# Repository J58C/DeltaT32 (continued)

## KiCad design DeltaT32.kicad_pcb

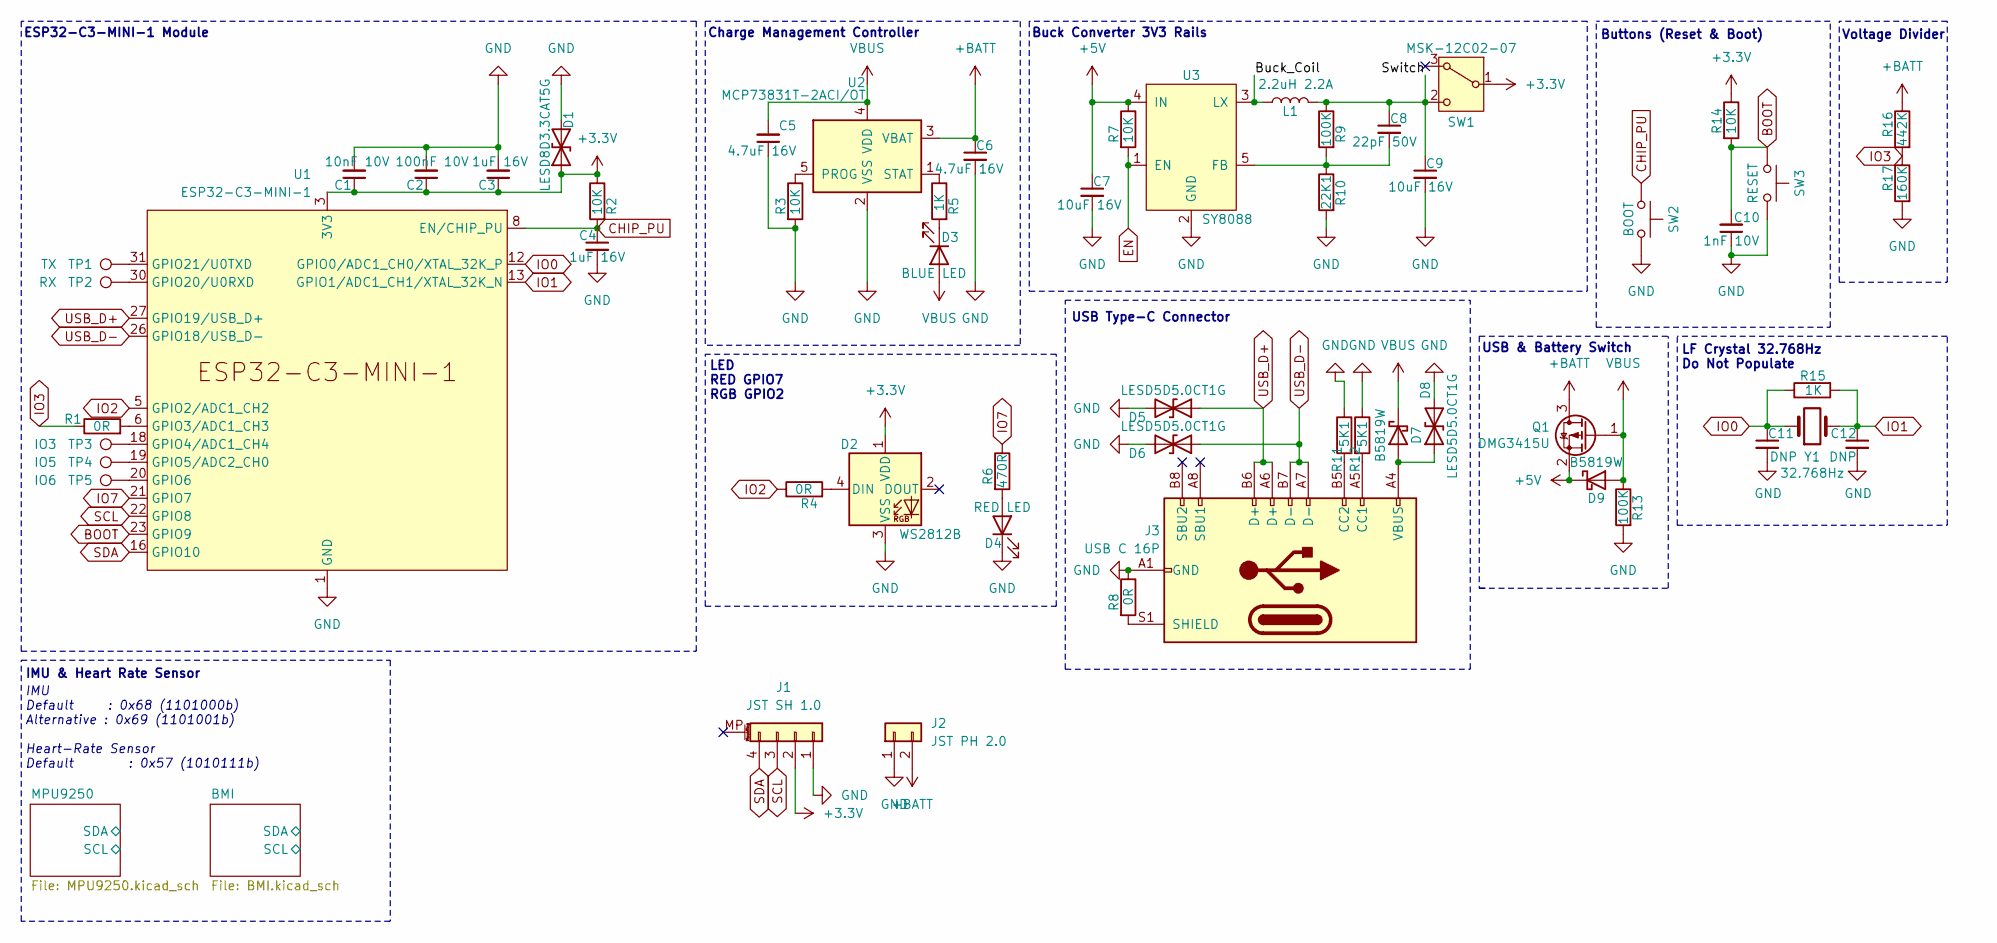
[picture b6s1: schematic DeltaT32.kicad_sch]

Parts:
C1: 10nF 10V; C_0402_1005Metric; LCSC C15195
C2: 100nF 10V; C_0402_1005Metric; LCSC C1525
C3, C4: 1uF 16V; C_0402_1005Metric; LCSC C52923
C5, C6: 4.7uF 16V; C_0603_1608Metric; LCSC C19666
C7, C9: 10uF 16V; C_0805_2012Metric; LCSC C15850
C8: 22pF 50V; C_0603_1608Metric; LCSC C1653
C10: 1nF 10V; C_0402_1005Metric; LCSC C1523
C11, C12: DNP; C_0402_1005Metric
D1: LESD8D3.3CAT5G; D_SOD-882; LCSC C172409
D2: WS2812B; LED_WS2812B-2020_PLCC4_2.0x2.0mm
D3: BLUE LED; LED_0603_1608Metric
D4: RED LED; LED_0603_1608Metric; LCSC C2286
D5, D6, D8: LESD5D5.0CT1G; D_SOD-523; LCSC C383211
D7, D9: B5819W; D_SOD-123; LCSC C8598
J1: JST SH 1.0; JST_SH_SM04B-SRSS-TB_1x04-1MP_P1.00mm_Horizontal
J2: JST PH 2.0; JST_PH_S2B-PH-K_1x02_P2.00mm_Horizontal
J3: USB C 16P; USB_C_Receptacle_GCT_USB4105-xx-A_16P_TopMnt_Horizontal
L1: 2.2uH 2.2A; L_Bourns-SRN4018; LCSC C370436
Q1: DMG3415U; SOT-23; LCSC C96616
R1, R4, R8: 0R; R_0402_1005Metric
R2, R3, R7, R14: 10K; R_0402_1005Metric
R5, R15: 1K; R_0402_1005Metric
R6: 470R; R_0402_1005Metric
R9, R13: 100K; R_0402_1005Metric
R10: 22K1; R_0402_1005Metric
R11, R12: 5K1; R_0402_1005Metric
R16: 442K; R_0805_2012Metric
R17: 160K; R_0805_2012Metric
SW1: MSK-12C02-07; SW_SPDT_PCM12
SW2: BOOT; SW_Push_SPST_NO_Alps_SKRK
SW3: RESET; SW_Push_SPST_NO_Alps_SKRK
TP1: TX; TestPoint_Pad_D1.0mm
TP2: RX; TestPoint_Pad_D1.0mm
TP3: IO3; TestPoint_Pad_D1.0mm
TP4: IO5; TestPoint_Pad_D1.0mm
TP5: IO6; TestPoint_Pad_D1.0mm
U1: ESP32-C3-MINI-1
U2: MCP73831T-2ACI/OT; SOT-23-5; LCSC C424093
U3: SY8088; SOT-23-5; LCSC C479072
Y1: 32.768Hz; Crystal_SMD_3215-2Pin_3.2x1.5mm

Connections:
+3.3V: C1.1, C2.1, C3.1, D1.1 (A1), D2.1 (VDD), J1.2, R2.1, R14.1, SW1.1 (B), U1.3 (3V3)
+5V: C7.1, D9.1 (K), Q1.2 (S), R7.1, U3.4 (IN)
+BATT: C6.1, J2.2, Q1.3 (D), R16.1, U2.3 (VBAT)
/Buck_Coil: L1.1, U3.3 (LX)
/Switch: C8.1, C9.1, L1.2, R9.1, SW1.2 (C)
BOOT: C10.2, R14.2, SW3.1, U1.23 (GPIO9)
CHIP_PU: C4.1, R2.2, SW2.1, U1.8 (EN/CHIP_PU)
EN: R7.2, U3.1 (EN)
GND: C1.2, C2.2, C3.2, C4.2, C5.1, C6.2, C7.2, C9.2, C10.1, C11.2, C12.2, D1.2 (A2), D2.3 (VSS), D4.1 (K), D5.2 (A2), D6.2 (A2), D8.2 (A2), J1.1, J2.1, J3.A1 (GND), J3.A12 (GND), J3.B1 (GND), J3.B12 (GND), R3.2, R8.1, R10.2, R11.1, R12.1, R13.2, R17.2, SW2.2, SW3.2, U1.1 (GND), U1.2 (GND), U1.11 (GND), U1.14 (GND), U1.36 (GND), U1.37 (GND), U1.38 (GND), U1.39 (GND), U1.40 (GND), U1.41 (GND), U1.42 (GND), U1.43 (GND), U1.44 (GND), U1.45 (GND), U1.46 (GND), U1.47 (GND), U1.48 (GND), U1.49 (GND), U1.50 (GND), U1.51 (GND), U1.52 (GND), U1.53 (GND), U2.2 (VSS), U3.2 (GND); also elsewhere on the board
IO0: C11.1, R15.1, U1.12 (GPIO0/ADC1_CH0/XTAL_32K_P), Y1.1
IO1: C12.1, R15.2, U1.13 (GPIO1/ADC1_CH1/XTAL_32K_N), Y1.2
IO2: R4.1, U1.5 (GPIO2/ADC1_CH2)
IO3: R1.1, R16.2, R17.1
IO7: R6.1, U1.21 (GPIO7)
unnamed: D2.4 (DIN), R4.2
unnamed: D3.1 (K), R5.2
unnamed: D4.2 (A), R6.2
unnamed: D7.2 (A), D8.1 (A1), J3.A4 (VBUS), J3.A9 (VBUS), J3.B4 (VBUS), J3.B9 (VBUS)
unnamed: J3.A5 (CC1), R12.2
unnamed: J3.B5 (CC2), R11.2
unnamed: J3.S1 (SHIELD), R8.2
unnamed: R1.2, U1.6 (GPIO3/ADC1_CH3)
unnamed: TP3.1, U1.18 (GPIO4/ADC1_CH4)
unnamed: TP4.1, U1.19 (GPIO5/ADC2_CH0)
unnamed: TP5.1, U1.20 (GPIO6)
unnamed: TP2.1, U1.30 (GPIO20/U0RXD)
unnamed: TP1.1, U1.31 (GPIO21/U0TXD)
unnamed: R3.1, U2.5 (PROG)
unnamed: R5.1, U2.1 (STAT)
unnamed: C8.2, R9.2, R10.1, U3.5 (FB)
SCL: J1.3, U1.22 (GPIO8); also elsewhere on the board
SDA: J1.4, U1.16 (GPIO10); also elsewhere on the board
USB_D+: D5.1 (A1), J3.A6 (D+), J3.B6 (D+), U1.27 (GPIO19/USB_D+)
USB_D-: D6.1 (A1), J3.A7 (D-), J3.B7 (D-), U1.26 (GPIO18/USB_D-)
VBUS: C5.2, D3.2 (A), D7.1 (K), D9.2 (A), Q1.1 (G), R13.1, U2.4 (VDD)

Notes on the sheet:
Buck Converter 3V3 Rails
Voltage Divider
IMU & Heart Rate Sensor
Buttons (Reset & Boot)
Charge Management Controller
USB & Battery Switch
LF Crystal 32.768Hz Do Not Populate
USB Type-C Connector
IMU Default : 0x68 (1101000b) Alternative : 0x69 (1101001b) Heart-Rate Sensor Default : 0x57 (1010111b)
ESP32-C3-MINI-1 Module
LED RED GPIO7 RGB GPIO2

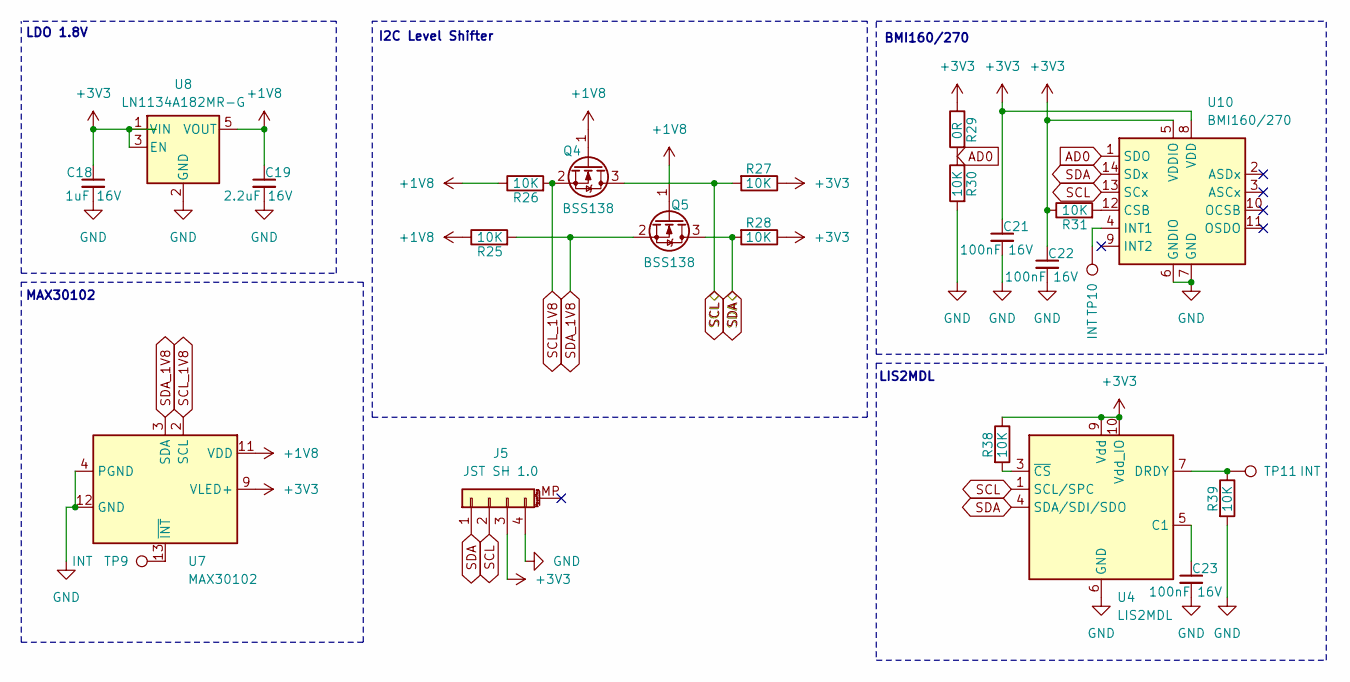
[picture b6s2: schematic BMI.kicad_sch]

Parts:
C18: 1uF 16V; C_0603_1608Metric
C19: 2.2uF 16V; C_0603_1608Metric
C21, C22, C23: 100nF 16V; C_0603_1608Metric
J5: JST SH 1.0; JST_SH_SM04B-SRSS-TB_1x04-1MP_P1.00mm_Horizontal
Q4, Q5: BSS138; SOT-23
R25, R26, R27, R28, R31, R38, R39: 10K; R_0603_1608Metric
R29: 0R; R_0402_1005Metric
R30: 10K; R_0402_1005Metric
TP9, TP10, TP11: INT; TestPoint_Pad_D1.0mm
U4: LIS2MDL; LGA-12_2x2mm_P0.5mm
U7: MAX30102; Maxim_OLGA-14_3.3x5.6mm_P0.8mm
U8: LN1134A182MR-G; SOT-23-5
U10: BMI160/270; Bosch_LGA-14_3x2.5mm_P0.5mm; LCSC C2836813

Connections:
+1V8: C19.1, Q4.1 (G), Q5.1 (G), R25.1, R26.1, U7.11 (VDD), U8.5 (VOUT); also elsewhere on the board
AD0: R29.2, R30.1, U10.1 (SDO); also elsewhere on the board
GND: C18.2, C19.2, C21.2, C22.2, C23.2, J5.4, R30.2, R39.2, U4.6 (GND), U4.8 (GND), U7.4 (PGND), U7.12 (GND), U8.2 (GND), U10.6 (GNDIO), U10.7 (GND); also elsewhere on the board
unnamed: C23.1, U4.5 (C1)
unnamed: R39.1, TP11.1, U4.7 (DRDY)
unnamed: R38.2, U4.3 (~CS)
unnamed: TP9.1, U7.13 (~INT)
unnamed: R31.2, U10.12 (CSB)
unnamed: TP10.1, U10.4 (INT1)
SCL: J5.2, Q4.3 (D), R27.2, U4.1 (SCL/SPC), U10.13 (SCx); also elsewhere on the board
SCL_1V8: Q4.2 (S), R26.2, U7.2 (SCL); also elsewhere on the board
SDA: J5.1, Q5.3 (D), R28.2, U4.4 (SDA/SDI/SDO), U10.14 (SDx); also elsewhere on the board
SDA_1V8: Q5.2 (S), R25.2, U7.3 (SDA); also elsewhere on the board
VDDIO: C18.1, C21.1, C22.1, J5.3, R27.1, R28.1, R29.1, R31.1, R38.1, U4.9 (Vdd), U4.10 (Vdd_IO), U7.9 (VLED+), U7.10 (VLED+), U8.1 (VIN), U8.3 (EN), U10.5 (VDDIO), U10.8 (VDD); also elsewhere on the board

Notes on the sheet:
MAX30102
LIS2MDL
LDO 1.8V
BMI160/270
I2C Level Shifter

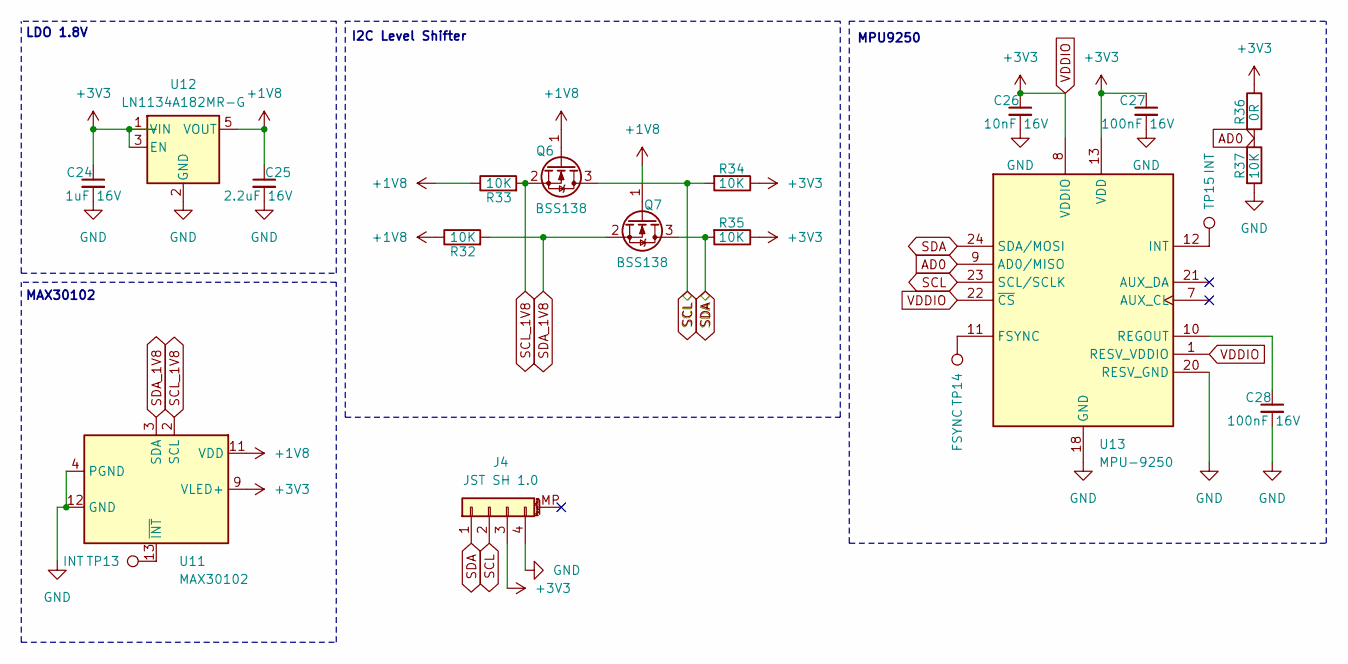
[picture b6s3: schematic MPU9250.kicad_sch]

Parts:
C24: 1uF 16V; C_0603_1608Metric
C25: 2.2uF 16V; C_0603_1608Metric
C26: 10nF 16V; C_0603_1608Metric
C27, C28: 100nF 16V; C_0603_1608Metric
J4: JST SH 1.0; JST_SH_SM04B-SRSS-TB_1x04-1MP_P1.00mm_Horizontal
Q6, Q7: BSS138; SOT-23
R32, R33, R34, R35: 10K; R_0603_1608Metric
R36: 0R; R_0402_1005Metric
R37: 10K; R_0402_1005Metric
TP13, TP15: INT; TestPoint_Pad_D1.0mm
TP14: FSYNC; TestPoint_Pad_D1.0mm
U11: MAX30102; Maxim_OLGA-14_3.3x5.6mm_P0.8mm
U12: LN1134A182MR-G; SOT-23-5
U13: MPU-9250; InvenSense_QFN-24_3x3mm_P0.4mm_NoMask

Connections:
+1V8: C25.1, Q6.1 (G), Q7.1 (G), R32.1, R33.1, U11.11 (VDD), U12.5 (VOUT); also elsewhere on the board
AD0: R36.2, R37.1, U13.9 (AD0/MISO); also elsewhere on the board
GND: C24.2, C25.2, C26.2, C27.2, C28.2, J4.4, R37.2, U11.4 (PGND), U11.12 (GND), U12.2 (GND), U13.18 (GND), U13.20 (RESV_GND); also elsewhere on the board
unnamed: TP13.1, U11.13 (~INT)
unnamed: TP14.1, U13.11 (FSYNC)
unnamed: TP15.1, U13.12 (INT)
unnamed: C28.1, U13.10 (REGOUT)
SCL: J4.2, Q6.3 (D), R34.2, U13.23 (SCL/SCLK); also elsewhere on the board
SCL_1V8: Q6.2 (S), R33.2, U11.2 (SCL); also elsewhere on the board
SDA: J4.1, Q7.3 (D), R35.2, U13.24 (SDA/MOSI); also elsewhere on the board
SDA_1V8: Q7.2 (S), R32.2, U11.3 (SDA); also elsewhere on the board
VDDIO: C24.1, C26.1, C27.1, J4.3, R34.1, R35.1, R36.1, U11.9 (VLED+), U11.10 (VLED+), U12.1 (VIN), U12.3 (EN), U13.1 (RESV_VDDIO), U13.8 (VDDIO), U13.13 (VDD), U13.22 (~CS); also elsewhere on the board

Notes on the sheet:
MAX30102
LDO 1.8V
MPU9250
I2C Level Shifter

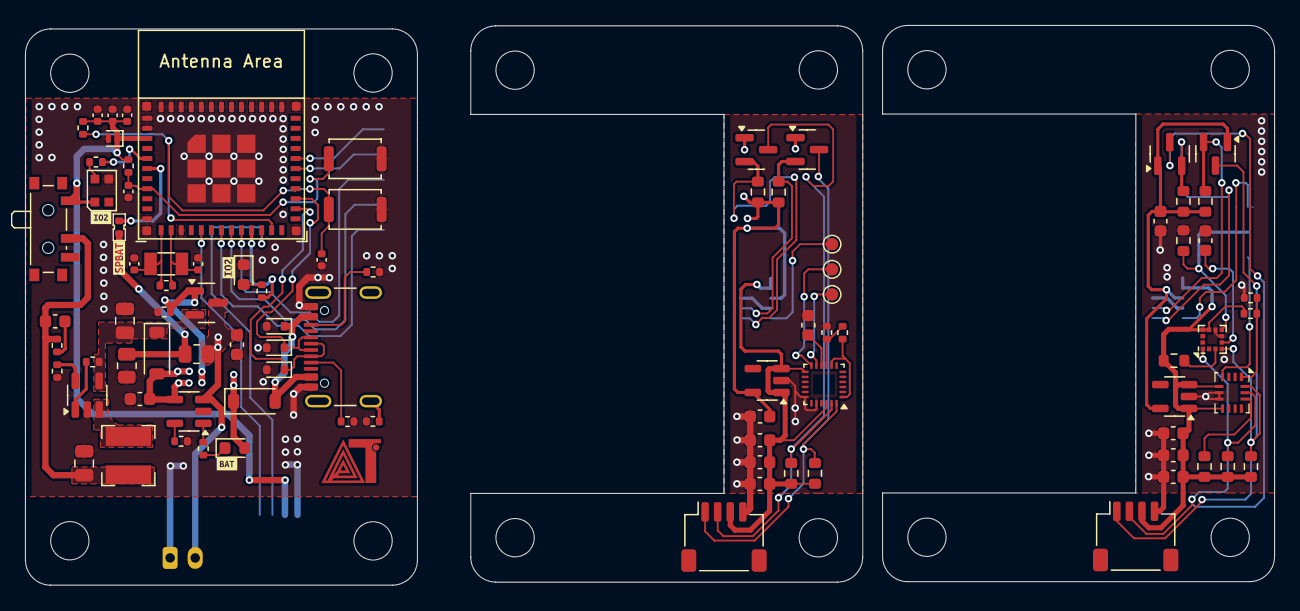
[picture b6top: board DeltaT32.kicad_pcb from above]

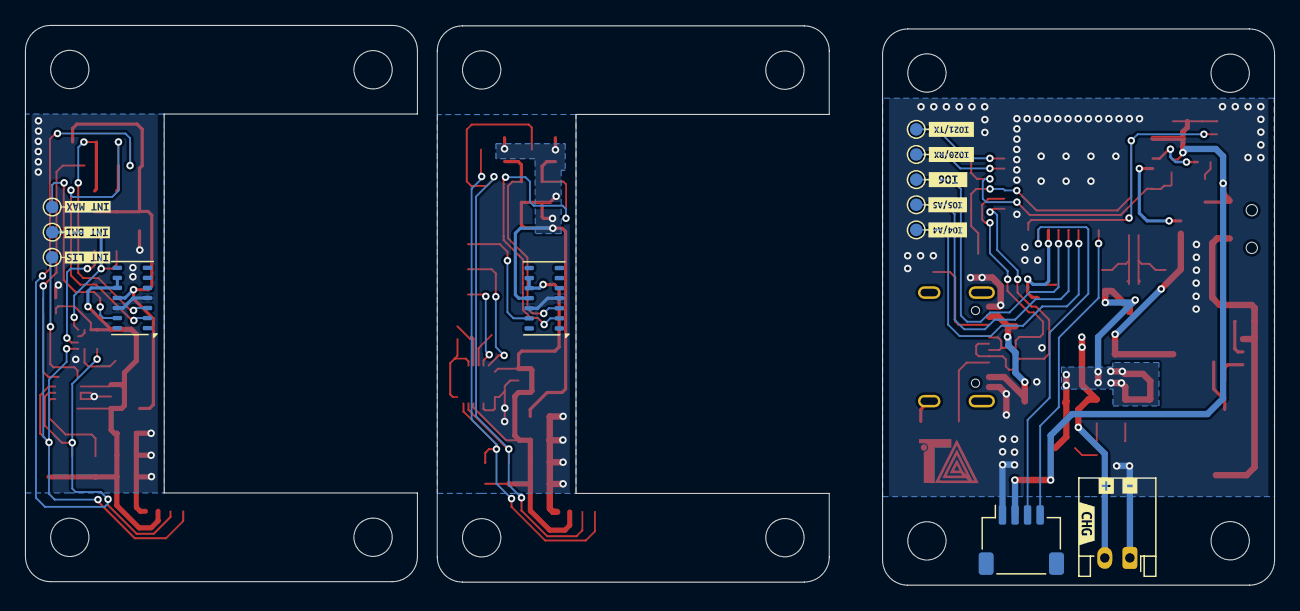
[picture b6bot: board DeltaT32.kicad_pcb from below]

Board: 2 copper layers, 99.4 x 44.5 mm, 103 parts (12 on the bottom side), 50 nets.

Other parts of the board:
kibuzzard-61C05335: G***; label
kibuzzard-67F4E109: G***; kibuzzard-67F4E109
kibuzzard-67FF2A33: G***; kibuzzard-67FF2A33
kibuzzard-6269032F: G***; kibuzzard-6269032F

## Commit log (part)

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2025-01-29 Twea
2025-01-29 Tweak
2025-01-29 Fix images workflow
2025-01-29 Update PCB render images for branch 17048
2025-01-29 Test
2025-01-29 Inital commit
2025-01-29 Initial file
2025-01-29 Update PCB render images
2025-01-29 Sync from 42 to main/42
2025-01-29 Sync from 17048 to main/17048
2025-01-29 Sync from 340 to main/340
2025-01-29 Create gif,yaml
2025-01-29 Update gif,yaml
2025-01-30 Add archive: 42-3001251053 from branch 42
2025-01-30 Add archive: Branch42-3001251058 from branch 42
2025-01-30 Add archive: Caps32Project-42-3001251131 from branch 42
2025-01-30 Update archive: Caps32Project-42-3001251133 from branch 42
2025-01-30 Update archive: Caps32Project-702-3001251140 from branch 702
2025-01-30 Update archive: Caps32Project-340-3001251202 from branch 340
2025-01-30 Update archive: Caps32Project-17048-3001251210 from branch 17048
2025-01-30 Update archive: Caps32Project-42-3001251211 from branch 42
2025-01-30 Update archive: Caps32Project-42-3001251311 from branch 42
2025-01-30 Update archive: Caps32Project-42-3001251318 from branch 42
2025-01-30 Update archive: Caps32Project-42-3001251326 from branch 42
2025-01-30 Update archive: Caps32Project-42-3001251333 from branch 42
2025-01-30 Update archive: Caps32Project-42-3001251345 from branch 42
2025-01-30 Update archive: Caps32Project-42-3001251407 from branch 42
2025-01-30 Move PCB render images from branch 42 to Images/42
2025-01-30 Update archive: Caps32Project-42-3001251414 from branch 42
2025-01-30 Update archive: Caps32Project-42-3001251421 from branch 42
2025-01-30 Update archive: Caps32Project-42-3001251425 from branch 42
2025-01-30 Update archive: Caps32Project-42-3001251430 from branch 42
2025-01-30 Update archive: Caps32Project-42-3001251445 from branch 42
2025-01-30 Update archive: Caps32Project-42-3001251450 from branch 42
2025-01-30 Update archive: Caps32Project-42-3001251458 from branch 42
2025-01-30 Update archive: Caps32Project-42-3001251505 from branch 42
2025-01-30 Update archive: Caps32Project-42-3001251510 from branch 42
2025-01-30 Move PCB render images from branch 42 to Images/42 and remove old images
2025-01-30 Update archive: Caps32Project-42-3001251514 from branch 42
2025-01-30 Update archive: Caps32Project-42-3001251611 from branch 42
2025-01-30 Update archive: Caps32Project-42-3001251629 from branch 42
2025-01-30 Update images: Rendered files
2025-01-30 Update archive: Caps32Project-42-3001251638 from branch 42
2025-01-30 Update archive: Caps32Project-42-3001251645 from branch 42
2025-01-30 Update archive: Caps32Project-42-3001251656 from branch 42
2025-01-31 Update archive: Caps32Project-17048-3101250133 from branch 17048
2025-01-31 Update archive: Caps32Project-17048-3101250140 from branch 17048
2025-01-31 Update archive: Caps32Project-340-3101250200 from branch 340
2025-01-31 Update archive: Caps32Project-340-3101250223 from branch 340
2025-01-31 Update archive: Caps32Project-340-3101250244 from branch 340
2025-01-31 Update archive: Caps32Project-340-3101250255 from branch 340
2025-01-31 Update archive: Caps32Project-702-3101250320 from branch 702
2025-01-31 Update archive: Caps32Project-42-3101250325 from branch 42
2025-01-31 Update archive: Caps32Project-17048-3101250334 from branch 17048
2025-01-31 Update images: Rendered files 17048
2025-01-31 Update archive: Caps32Project-17048-3101250649 from branch 17048
2025-01-31 Update archive: Caps32Project-17048-3101250656 from branch 17048
2025-01-31 Update archive: Caps32Project-17048-3101250657 from branch 17048
2025-01-31 Update archive: Caps32Project-17048-3101250700 from branch 17048
2025-01-31 Update archive: Caps32Project-17048-3101250705 from branch 17048
2025-01-31 Update archive: Caps32Project-17048-3101250706 from branch 17048
2025-01-31 Update archive: Caps32Project-17048-3101250710 from branch 17048
2025-01-31 Update archive: Caps32Project-17048-3101250751 from branch 17048
2025-01-31 Update archive: Caps32Project-17048-3101250755 from branch 17048
2025-01-31 Update archive: Caps32Project-17048-3101250806 from branch 17048
2025-01-31 Update archive: Caps32Project-17048-3101250811 from branch 17048
2025-01-31 Update archive: Caps32Project-17048-3101250825 from branch 17048
2025-01-31 Update archive: Caps32Project-17048-3101250828 from branch 17048
2025-02-01 Update archive: Caps32Project-4057-0102251340 from branch 4057
2025-02-01 Update images: Rendered files 4057
2025-02-01 Update archive: Caps32Project-42-0102251524 from branch 42
2025-02-01 Update images: Rendered files 42
2025-02-01 Update archive: Caps32Project-42-0102251529 from branch 42
2025-02-02 Update archive: Caps32Project-340-0202250328 from branch 340
2025-02-02 Update archive: Caps32Project-340-0202250331 from branch 340
2025-02-02 Update images: Rendered files 340
2025-02-02 Update archive: Caps32Project-17048-0202251233 from branch 17048
2025-02-02 Update archive: Caps32Project-17048-0202251412 from branch 17048
2025-02-02 Update archive: Caps32Project-702-0202251518 from branch 702
2025-02-02 Update images: Rendered files 702
2025-02-03 Update archive: Caps32Project-4057-0302250815 from branch 4057
2025-02-03 Update archive: Caps32Project-17048-0302251459 from branch 17048
2025-02-04 Update archive: Caps32Project-702-0402251052 from branch 702
2025-02-04 Update archive: Caps32Project-340-0402251238 from branch 340
2025-02-04 Update archive: Caps32Project-340-0402251350 from branch 340
2025-02-07 Update archive: Caps32Project-42-0702251243 from branch 42
2025-02-09 Update archive: Caps32Project-702-0902250951 from branch 702
2025-02-09 Update archive: Caps32Project-702-0902250957 from branch 702
2025-02-10 Update archive: Caps32Project-4057-1002250355 from branch 4057
2025-02-10 Update archive: Caps32Project-340-1002251438 from branch 340
2025-02-10 Update archive: Caps32Project-4057-1002251624 from branch 4057
2025-02-10 Update archive: Caps32Project-340-1002251628 from branch 340
2025-02-11 Update archive: Caps32Project-702-1102250424 from branch 702
2025-02-11 Update archive: Caps32Project-340-1102250431 from branch 340
2025-02-11 Update archive: Caps32Project-42-1102250747 from branch 42
2025-02-11 Update archive: Caps32Project-17048-1102251431 from branch 17048
2025-02-14 Update archive: Caps32Project-17048-1402250846 from branch 17048
2025-02-14 Update archive: Caps32Project-17048-1402251440 from branch 17048
2025-02-14 Update archive: Caps32Project-17048-1402251450 from branch 17048
2025-02-14 Update archive: Caps32Project-340-1402251520 from branch 340
2025-02-14 Update archive: Caps32Project-340-1402251703 from branch 340
2025-02-14 Update archive: Caps32Project-17048-1402251713 from branch 17048
2025-02-14 Update archive: Caps32Project-340-1402251724 from branch 340
2025-02-15 Update archive: Caps32Project-340-1502250144 from branch 340
2025-02-15 Update archive: Caps32Project-17048-1502250147 from branch 17048
2025-02-15 Update archive: Caps32Project-702-1502250846 from branch 702
2025-02-15 Update archive: Caps32Project-702-1502250924 from branch 702
2025-02-15 Update archive: Caps32Project-6206-1502250946 from branch 6206
2025-02-15 Update images: Rendered files 6206
2025-02-15 Update archive: Caps32Project-6206-1502251028 from branch 6206
2025-02-15 Update archive: Caps32Project-702-1502251035 from branch 702
2025-02-15 Update archive: Caps32Project-6206-1502251037 from branch 6206
2025-02-15 Update archive: Caps32Project-4057-1502251117 from branch 4057
2025-02-15 Update archive: Caps32Project-9250-1502251544 from branch 9250
2025-02-15 Update images: Rendered files 9250
2025-02-15 Update archive: Caps32Project-42-1502251553 from branch 42
2025-02-15 Update archive: Caps32Project-42-1502251600 from branch 42
2025-02-15 Update archive: Caps32Project-9250-1502251609 from branch 9250
2025-02-15 Update archive: Caps32Project-702-1502251621 from branch 702
2025-02-15 Update archive: Caps32Project-6206-1502251629 from branch 6206
2025-02-16 Update archive: UW-340-1602250653 from branch 340
2025-02-16 Update archive: UW-340-1602250708 from branch 340
2025-02-16 Update archive: mC3-42-1602250710 from branch 42
2025-02-16 Update archive: iS2-17048-1602250724 from branch 17048
2025-02-16 Update archive: S3-1-702-1602250730 from branch 702
2025-02-16 Update archive: S3-1-702-1602250743 from branch 702
2025-02-16 Update archive: C3-1-4057-1602250753 from branch 4057
2025-02-16 Update archive: C3-2-9250-1602250755 from branch 9250
2025-02-16 Update archive: S3-2-6206-1602250801 from branch 6206
2025-02-16 Update archive: UW-340-1602250804 from branch 340
2025-02-16 Update archive: S3-2-6206-1602250830 from branch 6206
2025-02-16 Update archive: C3-1-4057-1602250843 from branch 4057
2025-02-16 Update archive: mC3-42-1602250956 from branch 42
2025-02-16 Update archive: mC3-42-1602251207 from branch 42
2025-02-16 Update archive: mC3-42-1602251211 from branch 42
2025-02-16 Update archive: mC3-42-1602251213 from branch 42
2025-02-16 Update archive: mC3-42-1602251228 from branch 42
2025-02-16 Update archive: mC3-42-1602251235 from branch 42
2025-02-16 Update images: Rendered files AIO
2025-02-16 Update archive: UW-340-1602251638 from branch 340
2025-02-17 Update archive: mC3-42-1702250237 from branch 42
2025-03-02 Update archive: iS2-17048-0203250704 from branch 17048
2025-04-08 Baseline
2025-04-08 Update Test
2025-04-08 Up
    Upgrade kicad version
2025-04-08 Update PCB render images for main
2025-04-10 Update Board
2025-04-26 Downgrade and pcb breakdown
2025-04-28 add sensor board
2025-04-29 panelize sensor board
2025-05-01 resizing pcb board
2025-05-04 update esp board
2025-05-04 materials and schematic
2025-05-04 Merge pull request #4 from J58C/010525
    010525
2025-05-10 Update for poduction
2025-05-10 adjustable repo
2025-05-10 Create LICENSE
